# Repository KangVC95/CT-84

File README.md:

# CT-84
 Our first keyboard PCB from Crew-T

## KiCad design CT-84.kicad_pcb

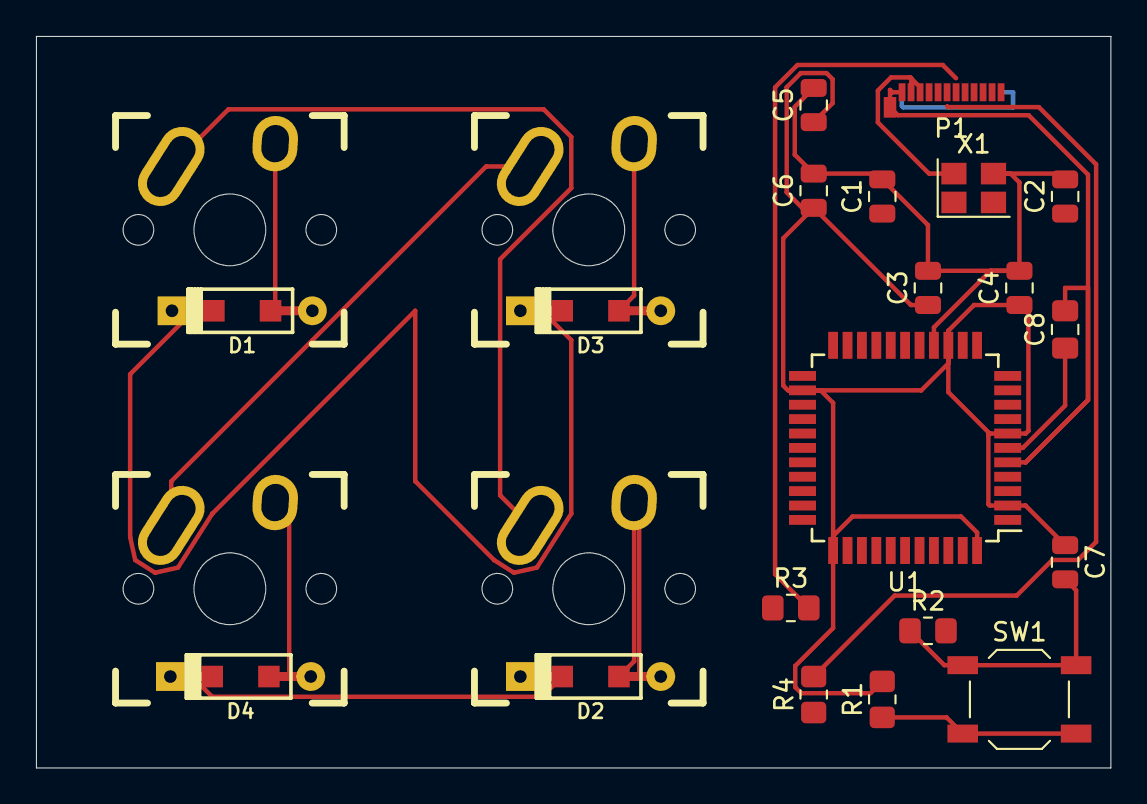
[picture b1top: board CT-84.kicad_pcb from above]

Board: 2 copper layers, 59.7 x 40.6 mm, 24 parts (0 on the bottom side), 20 nets.

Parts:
C1, C2: 22p; C_0805_2012Metric
C3, C4, C5, C6: 0.1u; C_0805_2012Metric
C7: 4.7u; C_0805_2012Metric
C8: 1u; C_0805_2012Metric_Pad1.18x1.45mm_HandSolder
D1, D2, D3, D4: D; D_SOD123_axial
K1, K2, K3, K4: KEYSW; Mx_Alps_100
P1: USB_C_Plug_USB2.0; USB_C_Plug_Molex_105444
R1, R2: 10k; R_0805_2012Metric_Pad1.20x1.40mm_HandSolder
R3, R4: 22; R_0805_2012Metric_Pad1.20x1.40mm_HandSolder
SW1: SW_PUSH; SW_SPST_TL3342
U1: ATMEGA32U4; TQFP-44_10x10mm_Pitch0.8mm
X1: XTAL_GND; Crystal_SMD_SeikoEpson_FA238-4Pin_3.2x2.5mm

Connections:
+5V: C8.2, P1.A1, P1.A12, P1.B1, P1.B12, P1.S1, U1.5
/col0: K1.1, K2.1, U1.39
/col1: K3.1, K4.1, U1.38
/row0: D1.1, D3.1, U1.41
/row1: D2.1, D4.1, U1.40
GND: C1.2, C2.2, C3.2, C4.2, C5.2, C6.2, C7.2, R2.1, SW1.1, U1.15, U1.23, U1.35, U1.43, X1.3
unnamed: C1.1, U1.16, X1.1
unnamed: C2.1, U1.17, X1.2
unnamed: C8.1, U1.6
unnamed: D1.2, K1.2
unnamed: D2.2, K2.2
unnamed: D3.2, K3.2
unnamed: D4.2, K4.2
unnamed: P1.A6, R4.2
unnamed: P1.A7, R3.2
unnamed: R1.1, SW1.2, U1.13
unnamed: R2.2, U1.33
unnamed: R3.1, U1.3
unnamed: R4.1, U1.4
VCC: C3.1, C4.1, C5.1, C6.1, C7.1, P1.A4, P1.A9, P1.B4, P1.B9, R1.2, U1.2, U1.7, U1.14, U1.24, U1.34, U1.44

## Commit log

2021-05-28 Update LICENSE
2021-05-28 files
